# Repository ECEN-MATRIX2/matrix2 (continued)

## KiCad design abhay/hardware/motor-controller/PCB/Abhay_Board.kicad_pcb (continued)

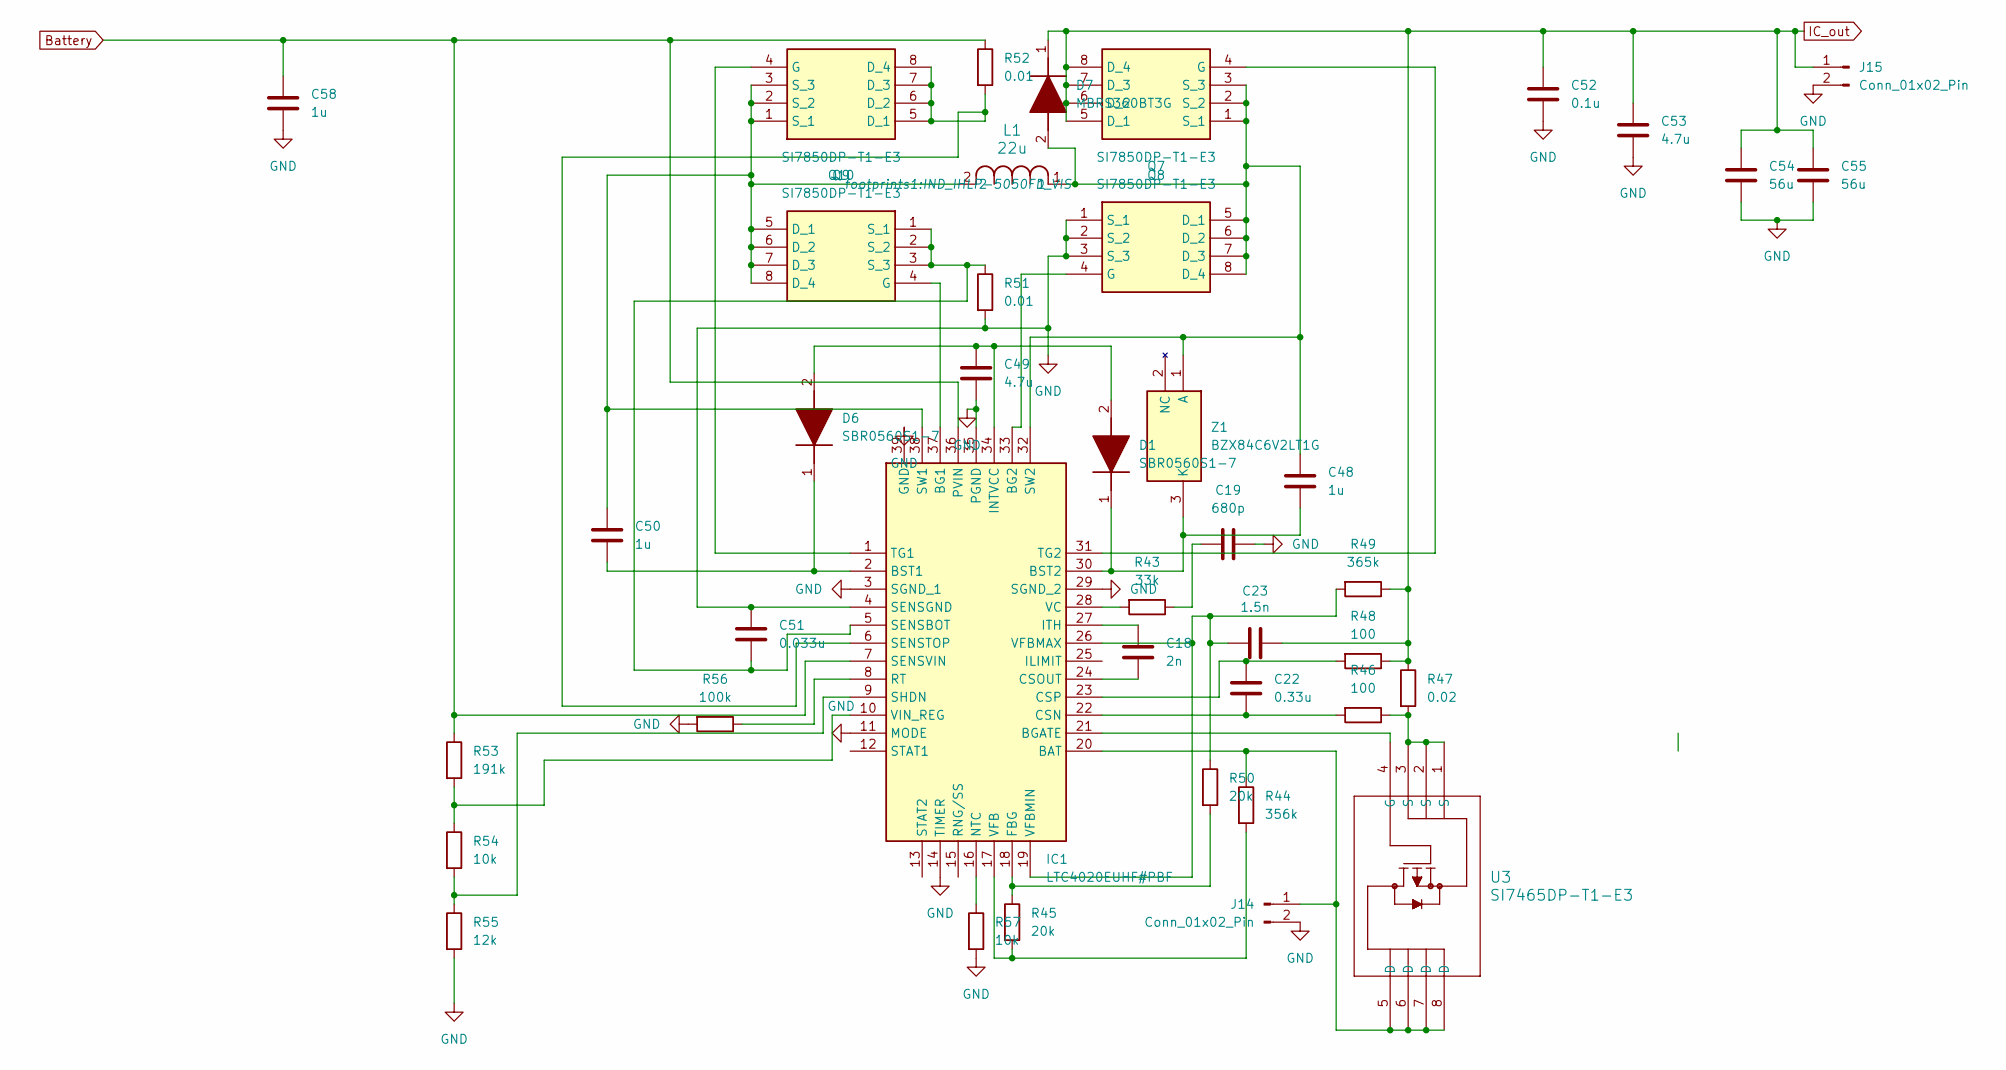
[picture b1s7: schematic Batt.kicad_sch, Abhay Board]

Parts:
C18: 2n; C_1206_3216Metric
C19: 680p; C_0603_1608Metric
C22: 0.33u; C_0603_1608Metric
C23: 1.5n; C_1206_3216Metric
C48, C58: 1u; C_1206_3216Metric
C49, C53: 4.7u; C_1206_3216Metric
C50: 1u; C_0603_1608Metric
C51: 0.033u; C_0603_1608Metric
C52: 0.1u; C_0603_1608Metric
C54, C55: 56u; C_Radial_D10.0mm_H12.5mm_P5.00mm
D1, D6: SBR0560S1-7; SOD3716X135N; Mouser Part Number 621-SBR0560S1-7-F
D7: MBRS360BT3G; DIOM5436X247N; Mouser Part Number 863-MBRS360BT3G
IC1: LTC4020EUHF#PBF; QFN50P500X700X80-39N-D; Mouser Part Number N/A
J14, J15: Conn_01x02_Pin; PinHeader_1x02_P2.54mm_Vertical
L1: 22u; IND_IHLP-5050FD_VIS
Q7, Q8, Q9, Q10: SI7850DP-T1-E3; SI7141DPT1GE3; Mouser Part Number 781-SI7850DP-E3
R43: 33k; R_0603_1608Metric
R44: 356k; R_0603_1608Metric
R45, R50: 20k; R_0603_1608Metric
R46, R48: 100; R_0603_1608Metric
R47: 0.02; R_0603_1608Metric
R49: 365k; R_0603_1608Metric
R51: 0.01; R_0603_1608Metric
R52: 0.01; R_2512_6332Metric
R53: 191k; R_0603_1608Metric
R54, R57: 10k; R_0603_1608Metric
R55: 12k; R_0603_1608Metric
R56: 100k; R_0603_1608Metric
U3: SI7465DP-T1-E3; PowerPAK_SO-8_VIS
Z1: BZX84C6V2LT1G; SOT96P237X111-3N; Mouser Part Number 863-BZX84C6V2LT1G

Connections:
Battery: C58.1, IC1.7 (SENSVIN), IC1.36 (PVIN), R52.1, R53.1; also elsewhere on the board
GND: C19.1, C49.1, C51.1, C52.2, C53.2, C54.2, C55.2, C58.2, IC1.3 (SGND_1), IC1.4 (SENSGND), IC1.11 (MODE), IC1.14 (TIMER), IC1.29 (SGND_2), IC1.35 (PGND), IC1.39 (GND), J14.2, J15.2, Q7.1 (S_1), Q7.2 (S_2), Q7.3 (S_3), R51.2, R55.2, R56.2, R57.2; also elsewhere on the board
IC_out: C23.2, C52.1, C53.1, C54.1, C55.1, D7.1 (K), J15.1, Q8.5 (D_1), Q8.6 (D_2), Q8.7 (D_3), Q8.8 (D_4), R47.1, R48.1, R49.1
unnamed: C19.2, R43.1
unnamed: C49.2, D1.2 (A), D6.2 (A), IC1.34 (INTVCC)
unnamed: C48.2, D1.1 (K), IC1.30 (BST2), Z1.3 (K)
unnamed: C50.2, D6.1 (K), IC1.2 (BST1)
unnamed: C48.1, D7.2 (A), IC1.32 (SW2), L1.1, Q7.5 (D_1), Q7.6 (D_2), Q7.7 (D_3), Q7.8 (D_4), Q8.1 (S_1), Q8.2 (S_2), Q8.3 (S_3), Z1.1 (A)
unnamed: IC1.20 (BAT), J14.1, R44.1, U3.5 (D), U3.6 (D), U3.7 (D), U3.8 (D)
unnamed: IC1.37 (BG1), Q10.4 (G)
unnamed: IC1.33 (BG2), Q7.4 (G)
unnamed: IC1.21 (BGATE), U3.4 (G)
unnamed: C22.2, IC1.22 (CSN), R46.2
unnamed: C18.2, IC1.24 (CSOUT)
unnamed: C22.1, IC1.23 (CSP), R48.2
unnamed: IC1.18 (FBG), R45.1, R50.2
unnamed: C18.1, IC1.27 (ITH)
unnamed: IC1.16 (NTC), R57.1
unnamed: IC1.8 (RT), R56.1
unnamed: C51.2, IC1.5 (SENSBOT), Q10.1 (S_1), Q10.2 (S_2), Q10.3 (S_3), R51.1
unnamed: IC1.6 (SENSTOP), Q9.5 (D_1), Q9.6 (D_2), Q9.7 (D_3), Q9.8 (D_4), R52.2
unnamed: IC1.9 (SHDN), R54.2, R55.1
unnamed: C50.1, IC1.38 (SW1), L1.2, Q9.1 (S_1), Q9.2 (S_2), Q9.3 (S_3), Q10.5 (D_1), Q10.6 (D_2), Q10.7 (D_3), Q10.8 (D_4)
unnamed: IC1.1 (TG1), Q9.4 (G)
unnamed: IC1.31 (TG2), Q8.4 (G)
unnamed: IC1.28 (VC), R43.2
unnamed: IC1.17 (VFB), R44.2, R45.2
unnamed: C23.1, IC1.19 (VFBMIN), IC1.26 (VFBMAX), R49.2, R50.1
unnamed: IC1.10 (VIN_REG), R53.2, R54.1
unnamed: R46.1, R47.2, U3.1 (S), U3.2 (S), U3.3 (S)

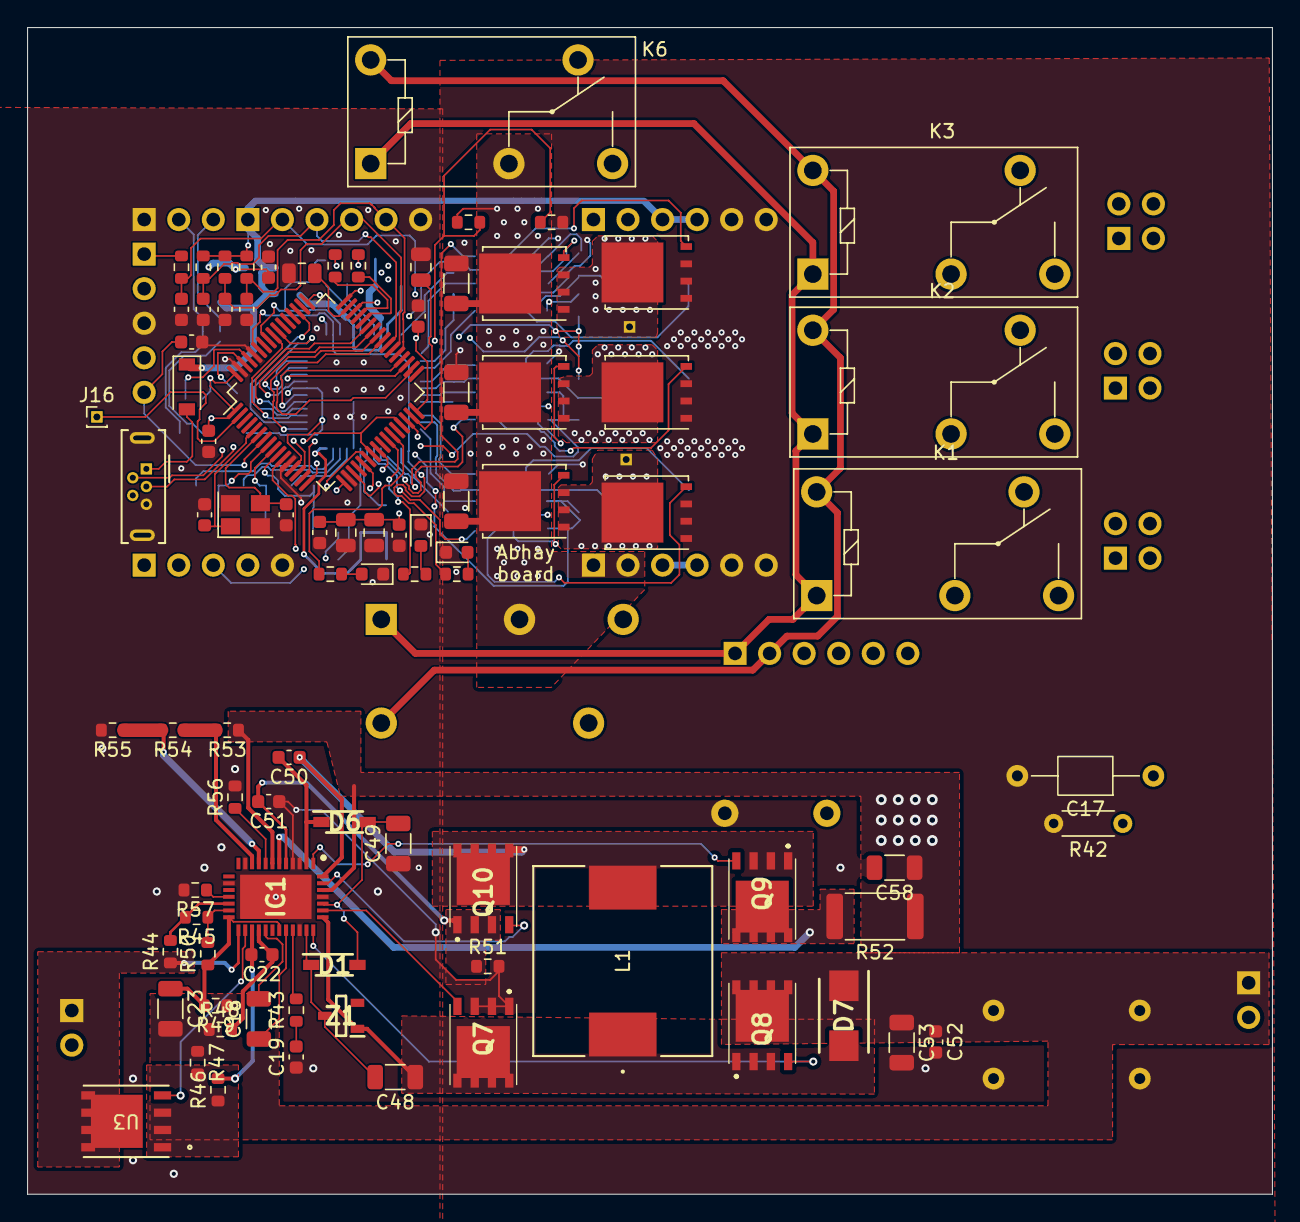
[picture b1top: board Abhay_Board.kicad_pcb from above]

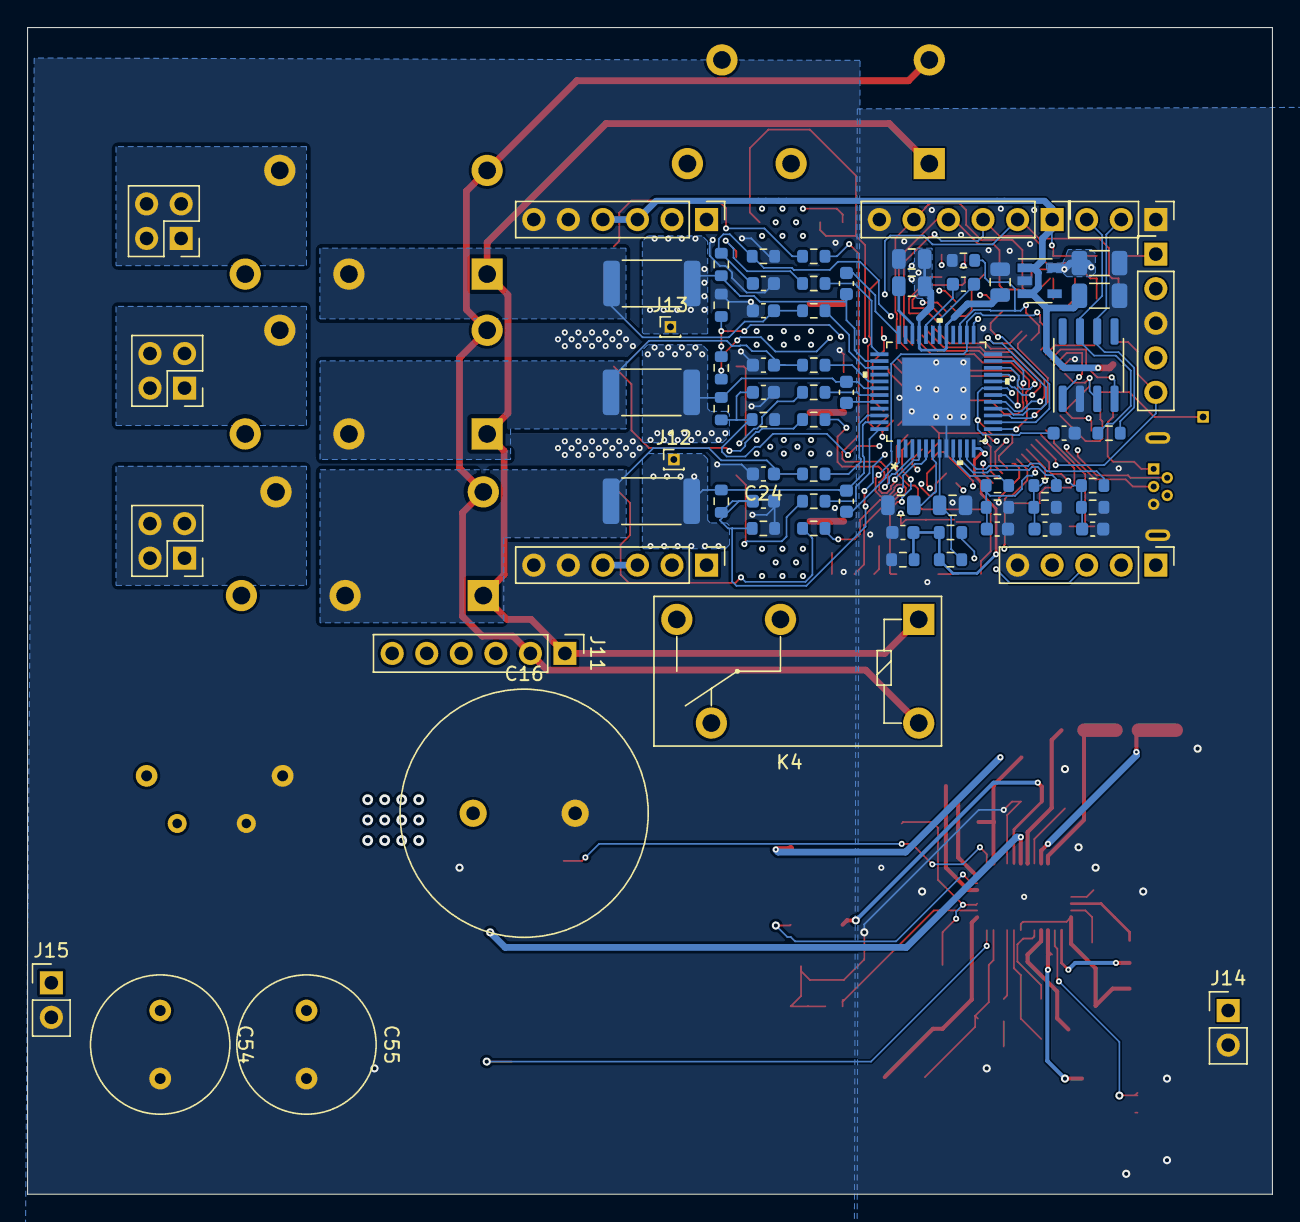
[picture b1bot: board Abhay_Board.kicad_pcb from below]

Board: 4 copper layers, 91.5 x 85.8 mm, 161 parts (74 on the bottom side), 120 nets.

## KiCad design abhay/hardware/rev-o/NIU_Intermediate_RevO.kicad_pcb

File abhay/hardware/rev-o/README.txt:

NIU INTERMEDIATE BOARD - REV O - RELAY 12 V PASS-THROUGH
Prepared 2026-10-08. Extract the complete ZIP, then open NIU_Intermediate_RevO.kicad_pro in KiCad 9.
Local symbol/footprint libraries and all fitted-component 3D models are included.

Rev O adds J14 beside J5. It is a second regular two-pin male header wired
directly in parallel with the external relay-control input, before diode D3.
All Rev N components, their values/MPNs, placements and original traces remain.
The 36 V buck, isolated 5 V, local sensing 3.3 V, SOC circuit and 5 V throttle
are unchanged. J13 remains removed; J14 is NOT a 3.3 V power connector.

  ONE external switched 12 V source -> J5
                                       | parallel, raw +12 V / coil return
                                       +-> J14 -> motor-board J11 pins 1 and 2

Header          Pin 1                    Pin 2
J5 12V IN       external +12 V           external coil return
J14 12V OUT     same external +12 V      same external coil return
Motor J11       Relay+                   Relay-

Connect J14 pin 1 to motor J11 pin 1 and J14 pin 2 to motor J11 pin 2.
Do not add a second power supply to J14, or connect COIL_RET to battery or
SYSTEM_RET. This is a pass-through, not a 12 V regulator. It applies the same
ON/OFF command to both boards and adds no intentional delay.

With five actual 12 V G5Q-1 SPDT motor-board coils, the combined nominal load
is about 0.20 A: 5 x 33.3 mA plus about 37 mA for this board. The motor CAD says
G5Q-1 but does not identify the fitted coil-voltage suffix; verify the parts.
Use a switched 12 V output rated for at least 0.3 A, preferably 0.5 A, and verify
voltage at both boards when all coils are on. This combined load exceeds the
earlier 100 mA preference for the intermediate board alone.
D3 and D4 protect only this board's branch; they do not provide reverse-polarity
or flyback protection for the raw J14 output. Retain/check the motor board and
source driver's appropriate coil suppression. Do not add an unreviewed common
clamp, since suppression can change relay release timing.

U11 generates the sensing interface's 3.3 V locally from the always-on isolated
5 V rail. U11/C36/C37 and the separate battery-domain U10 supply are retained.
No external 3.3 V feed is needed. Mode-switched grounding remains as below.

84 x 128 mm rectangle (3.31 x 5.04 in), four layers, 1 oz copper each layer.
No board growth. 120 fitted components plus four mounting holes: exactly one
extra header versus Rev N. Motor PCB and installed firmware were not modified
or operated while preparing this revision.

Ordering
Purchasing/NIU_RevO_BOM.xlsx: 57 Mouser SKUs, 119 purchased pieces for one board.
User-supplied XT60 makes 120 fitted parts. No spares included.
- New/empty cart: Mouser_RevO_Full_1Board.csv.
- Already bought Rev N: Mouser_RevO_Added_Since_RevN.csv, one extra header.
- Already bought Rev M: Mouser_RevO_Added_Since_RevM.csv, U11/C36/C37 only.
  Reuse the spare two-pin header previously assigned to removed J13 for J14.
- Already bought Rev L: Mouser_RevO_Added_Since_RevL.csv, 34 extra pieces.
Use only the list appropriate to the order already placed.
J14 is Harwin M20-9990245 / Mouser 855-M20-9990245, the existing header SKU.
There are 12 fitted two-pin headers. No new part number is introduced in Rev O.
Prior stock evidence is retained; the increased header quantity was not
rechecked in a live cart. No component or PCB order was placed.

Integration
J12.1 is SDA, J12.2 is SCL. SYSTEM_RET reaches the motor/comm boards through
the existing two-wire 5 V power connections. No connection to motor J3.1
or any other external 3.3 V rail is required. Do not tie 3.3 V regulators together.
SOC requires firmware integration and calibration. FIRMWARE_INTEGRATION.txt
retains the proposed motor-MCU bridge and GNSS-preserving UART arrangement.
That proposal repurposes PA5 from analog speed to software-I2C clock; do not
connect J12 while the old firmware drives PA5 as a DAC.

Power and mode operation
  Battery -> F1 10 A -> R33 sense shunt -> LM70860 synchronous buck -> D7 -> K1 NC -> VM
  Charger output -> R34 sense shunt -> K1 NO -> F3 10 A -> battery charge port
K1 NC 11-12 carries drive positive; NC 21-22 carries drive return.
K1 NO 33-34 carries charge positive; NO 43-44 carries charge return.
Coil 0 is positive; coil 1 is negative. One 12 V / 30 mA nominal coil is powered
only by the external mode source. LED/opto current is additional and the total
is about 37 mA for this board alone. J14 motor-coil current is additional.
12 V absent: NC drive contacts closed, NO charging contacts open.
12 V present: NC drive contacts open, NO charging contacts closed.
The forcibly guided NC/NO mechanism replaces independent relay timing. All four
contacts are used for power paths; there is no feedback contact or welded-contact
diagnostic circuit. This is not a certified complete safety control system.

Keep the external sequence: disable drive before transfer; assert 12 V, wait
one second, then start AC. Stop AC, wait one second, then remove 12 V. No precharge
was added. Near-zero steady load does not eliminate capacitor charging inrush.
The G7SA has a 6 A carry rating, but its full-current resistive DC switching
rating is 6 A at 30 VDC. Its 125 VDC maximum switching voltage is NOT permission
to switch 6 A at 125 V. Loaded 36-54.6 V transfer and capacitive making current
have not been qualified. Measure inrush and obtain an applicable load rating
before using this prototype for repeated high-voltage load transfer.

Isolation meaning
Both conductors of the inactive drive/charge path are disconnected by contacts.
The unchanged motor PCB joins VM, charge-input and MCU returns as SYSTEM_RET.
Battery charge/discharge negatives may also be internally shared. As accepted
by the user, the active mode can connect SYSTEM_RET to that mode's battery return.
U1 provides an isolated conversion barrier, but its output return is SYSTEM_RET;
it does not make MCU/comm/throttle permanently isolated from VM/charging ground.
The external coil circuit remains separate. No mains isolation claim is made.

Voltage and current limits
36 V is the nominal loaded VM target: the buck regulates about 36.48 V before
D7 and the delivered voltage depends on diode drop, load and tolerance. Maximum
battery input is 54.6 V. Nominal enable threshold is about 39.3 V; this buck needs
input headroom and cannot boost a depleted battery.
The converter IC is rated 6 A; this is NOT a 6 A or 10 A complete-board rating.
The two-pin headers are rated 3 A per contact MAXIMUM. The mating jumper contacts
and wire may be rated lower or have no documented current rating. Use an external
current limit chosen for the actual harness. Start bench checks at low current.
The retained 10 A fuses do not protect these jumper wires against overload.
No continuous current or peak-duration qualification has been performed.
The motor PCB's separate phase-contact limits remain unchanged.

D7 still dissipates heat (about 1 W at 2 A, dependent on temperature). Wider
copper does not replace thermal testing. The VM shunt remains limited incidental-
energy protection: about 38.5 V on, 37.5 V off and 0.31 A at threshold. It is not
a regen brake, guaranteed 40 V ceiling, or sustained-backdrive/buck-fault absorber.

Connections: pin 1 / pin 2
J1  XT60 battery positive / battery discharge negative
J2  VM nominal 36 V / SYSTEM_RET
J3  charger-IC output positive / SYSTEM_RET
J4  battery charge-port positive / battery charge-port negative
J5  external charge-mode 12 V INPUT / isolated coil return
J6  MCU 5 V / SYSTEM_RET
J7  communication-board 5 V / SYSTEM_RET
J8  throttle 5 V / SYSTEM_RET
J9  raw throttle signal / SYSTEM_RET
J10 divided throttle ADC signal / SYSTEM_RET
J11 active-low charge command / SYSTEM_RET (MCU 3.3 V pull-up)
J12 SOC SDA / SOC SCL (3.3 V I2C signals, NOT a power connector)
J14 external charge-mode 12 V PASS-THROUGH / isolated coil return
J2-J12 and J14 use regular 2-pin 2.54 mm male headers. They are unkeyed: follow pin numbers
and the +/return markings when mating jumper wires. Auxiliary 5 V stays on in
both modes. J11 is a mode input, not an MCU shutoff or contact-position feedback.
See FIRMWARE_INTEGRATION.txt for the existing motor-board GPIO connection.

Package and CAD checks
Seven schematic sheets, PCB/project, local libraries/models, BOM and ordering
files, schematic PDF, filled-copper/3D previews, Gerbers, PTH/NPTH drills,
assembly positions and verification reports are included.
ERC 0, DRC 0, unconnected 0, parity 0; 334 electrical pads match schematic/model.
45 filled zones, 182 through vias, 237 round holes. Minimum drill 0.30 mm.
No slots, overlapping holes, blind/buried vias or internal cutouts. Projected
3 mm copper spacing checked across all four layers and all isolation domains.
See FABRICATION.txt for the retained AdvancedPCB special process constraints.

Hardware validation
This is a CAD-checked prototype. BENCH_CHECKS.txt retains the existing thermal,
inrush, transient and sensing checks and adds local 3.3 V startup/shutdown tests.
J5/J14 wiring, combined coil load and turn-off transients also require checks.
No assembled Rev O board has been powered or tested.

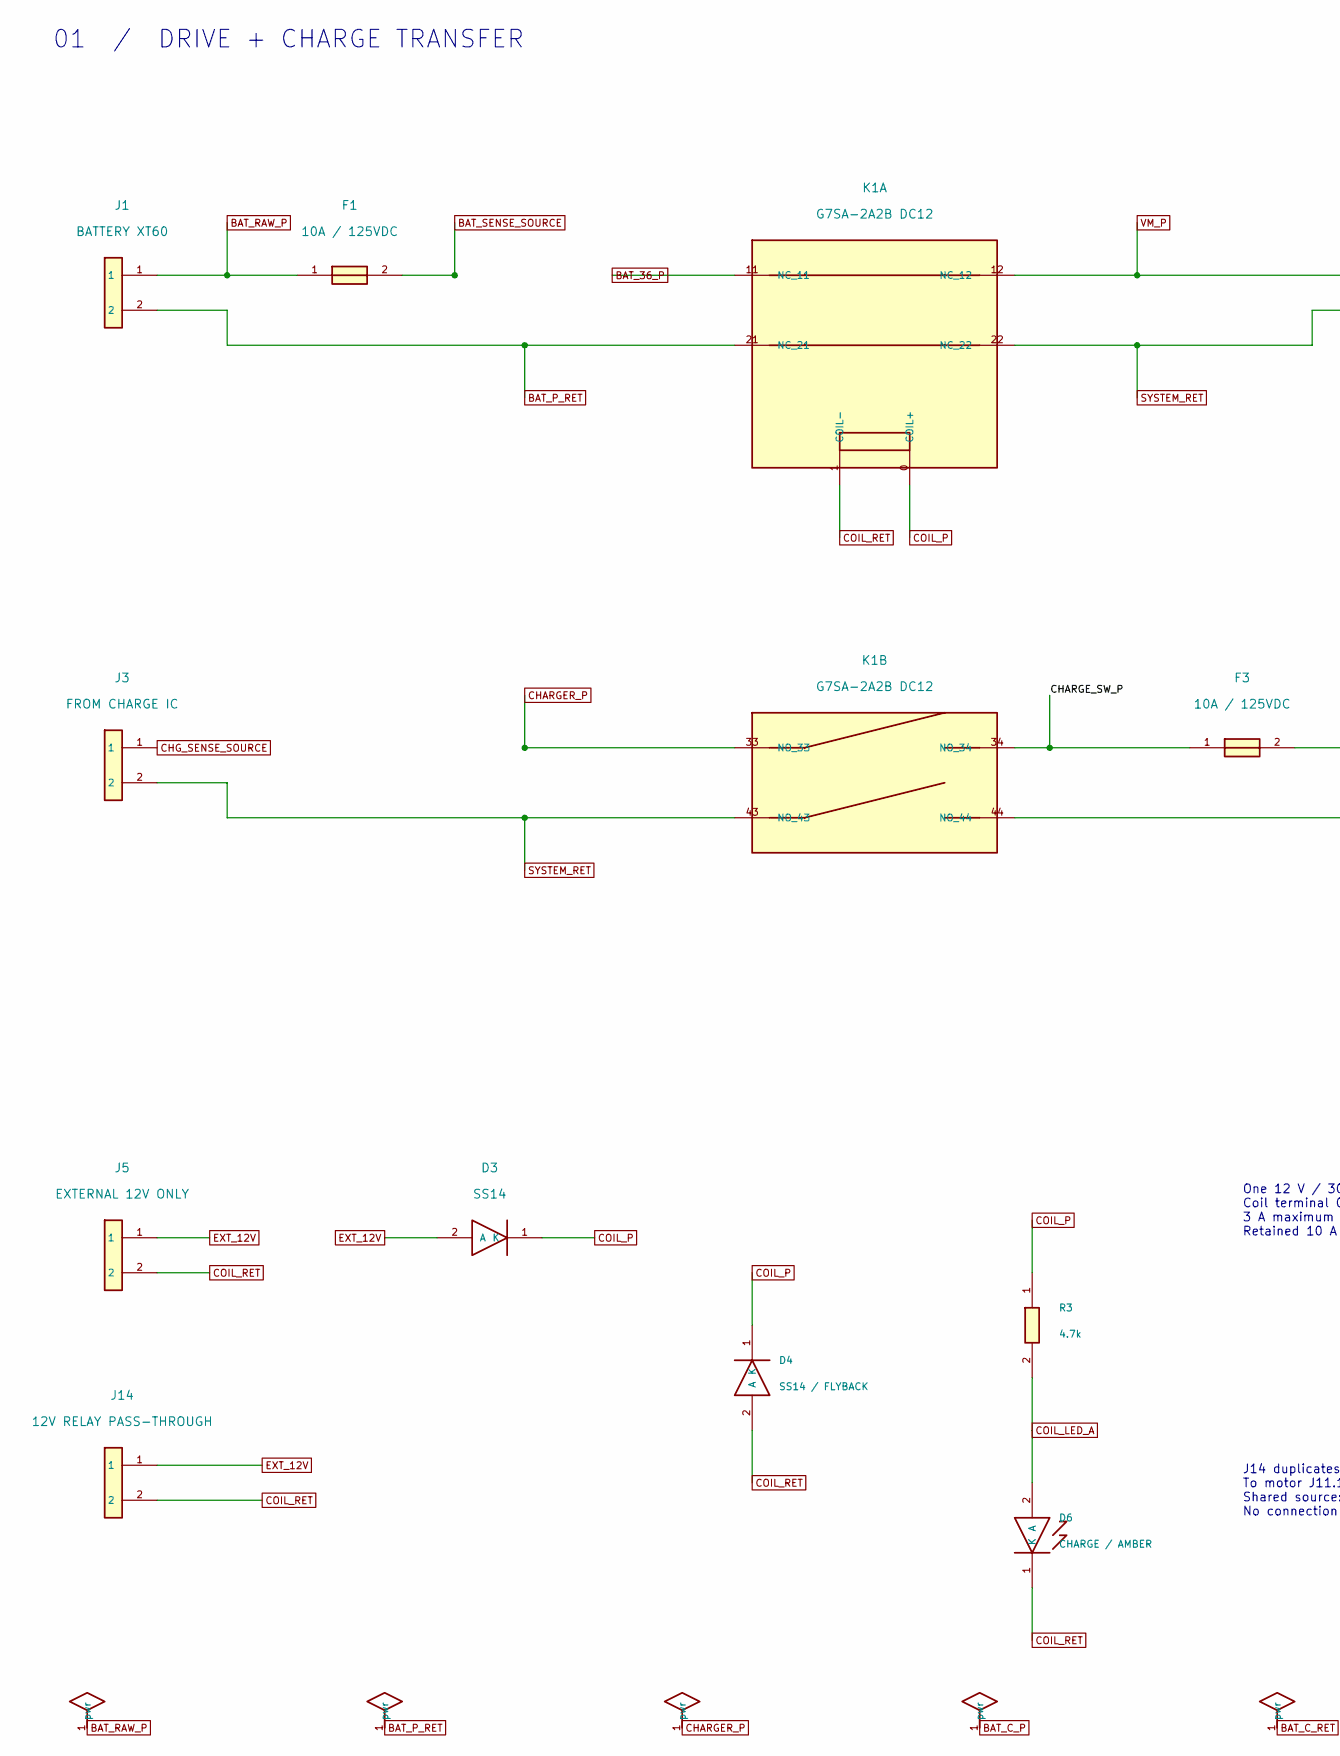
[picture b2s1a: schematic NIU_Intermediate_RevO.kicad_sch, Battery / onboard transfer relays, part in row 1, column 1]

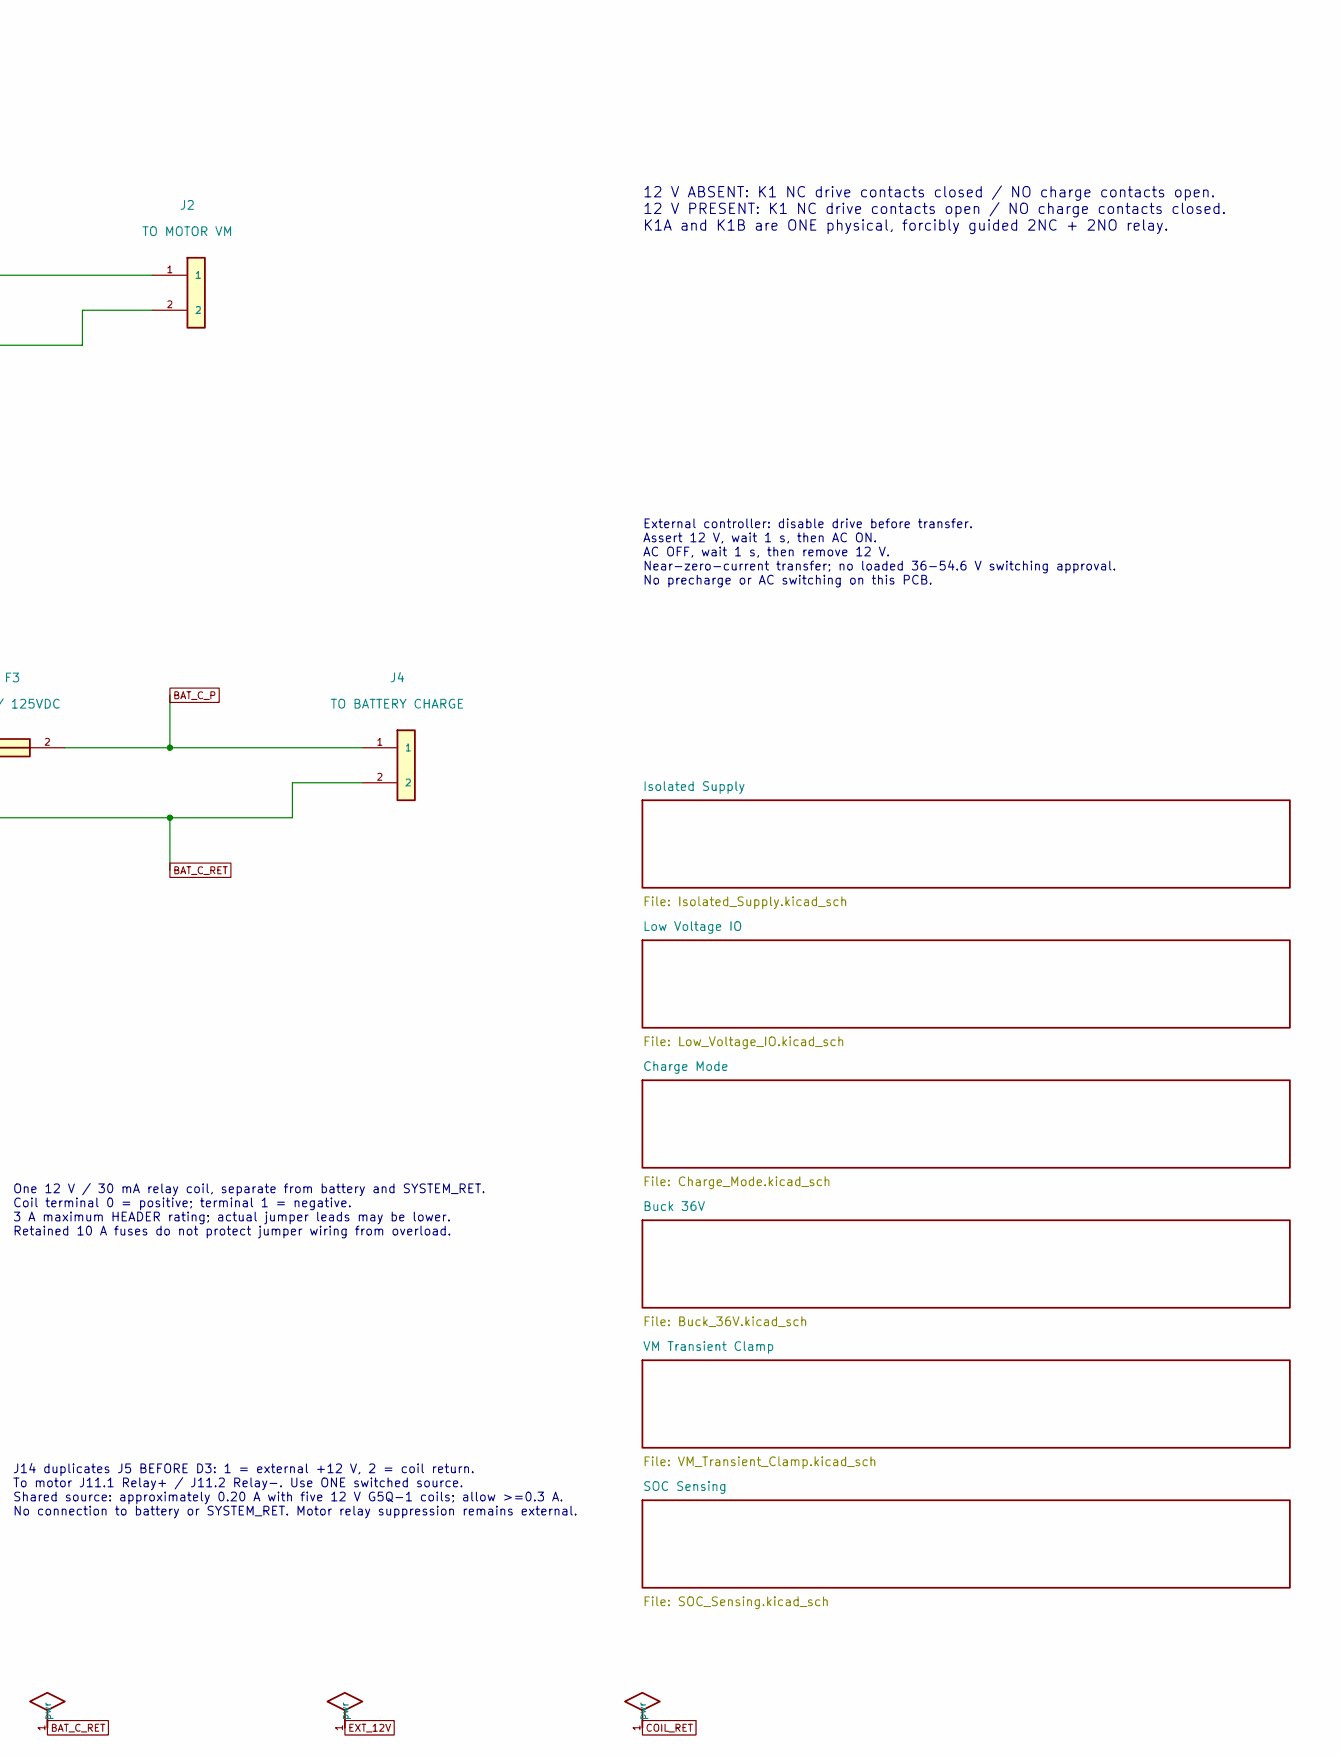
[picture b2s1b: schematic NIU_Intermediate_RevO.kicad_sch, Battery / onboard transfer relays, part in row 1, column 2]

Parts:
D3: SS14; D_SMA; Rating 40V 1A Schottky; MPN SS14-E3/61T; Mouser 625-SS14-E3
D4: SS14 / FLYBACK; D_SMA; Rating 40V 1A Schottky; MPN SS14-E3/61T; Mouser 625-SS14-E3
D6: CHARGE / AMBER; LED_0805_2012Metric; Rating 0805 amber; MPN LTST-C170KSKT; Mouser 859-LTST-C170KSKT
F1, F3: 10A / 125VDC; Fuse_SCHURTER_UMT-H_5.3x16; Rating 10A time lag; Schurter UMT-H; MPN 3403.0284.23; Mouser 693-3403.0284.23
J1: BATTERY XT60; AMASS_XT60-M_Vertical_PositivePin1; Rating 54.6V max intended pack; MPN XT60-M
J2: TO MOTOR VM; PinHeader_1x02_P2.54mm_Vertical; Rating 3A max per header contact; mating lead 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; MPN M20-9990245; Mouser 855-M20-9990245
J3: FROM CHARGE IC; PinHeader_1x02_P2.54mm_Vertical; Rating 3A max per header contact; mating lead 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; MPN M20-9990245; Mouser 855-M20-9990245
J4: TO BATTERY CHARGE; PinHeader_1x02_P2.54mm_Vertical; Rating 3A max per header contact; mating lead 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; MPN M20-9990245; Mouser 855-M20-9990245
J5: EXTERNAL 12V ONLY; PinHeader_1x02_P2.54mm_Vertical; Rating 3A header / LV signals; MPN M20-9990245; Mouser 855-M20-9990245
J14: 12V RELAY PASS-THROUGH; PinHeader_1x02_P2.54mm_Vertical; Rating 3A header / LV signals; MPN M20-9990245; Mouser 855-M20-9990245
K1: G7SA-2A2B DC12; Omron_G7SA_2A2B_TopView; Rating 2NC+2NO forcibly guided; 12V/30mA coil;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; MPN G7SA-2A2B DC12; Mouser 653-G7SA-2A2BDC12
R3: 4.7k; R_0805_2012Metric; Rating 1%, 0.125W; MPN RC0805FR-074K7L; Mouser 603-RC0805FR-074K7L

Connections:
/CHARGE_SW_P: F3.1, K1.34 (NO_34)
BAT_36_P: K1.11 (NC_11); also elsewhere on the board
BAT_C_P: F3.2, J4.1
BAT_C_RET: J4.2, K1.44 (NO_44)
BAT_P_RET: J1.2, K1.21 (NC_21); also elsewhere on the board
BAT_RAW_P: F1.1, J1.1
BAT_SENSE_SOURCE: F1.2; also elsewhere on the board
CHARGER_P: K1.33 (NO_33); also elsewhere on the board
CHG_SENSE_SOURCE: J3.1; also elsewhere on the board
COIL_LED_A: D6.2 (A), R3.2
COIL_P: D3.1 (K), D4.1 (K), K1.0 (COIL+), R3.1; also elsewhere on the board
COIL_RET: D4.2 (A), D6.1 (K), J5.2, J14.2, K1.1 (COIL-); also elsewhere on the board
EXT_12V: D3.2 (A), J5.1, J14.1
SYSTEM_RET: J2.2, J3.2, K1.22 (NC_22), K1.43 (NO_43); also elsewhere on the board
VM_P: J2.1, K1.12 (NC_12); also elsewhere on the board

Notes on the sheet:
01 / DRIVE + CHARGE TRANSFER
12 V ABSENT: K1 NC drive contacts closed / NO charge contacts open. 12 V PRESENT: K1 NC drive contacts open / NO charge contacts closed. K1A and K1B are ONE physical, forcibly guided 2NC + 2NO relay.
External controller: disable drive before transfer. Assert 12 V, wait 1 s, then AC ON. AC OFF, wait 1 s, then remove 12 V. Near-zero-current transfer; no loaded 36-54.6 V switching approval. No precharge or AC switching on this PCB.
One 12 V / 30 mA relay coil, separate from battery and SYSTEM_RET. Coil terminal 0 = positive; terminal 1 = negative. 3 A maximum HEADER rating; actual jumper leads may be lower. Retained 10 A fuses do not protect jumper wiring from overload.
J14 duplicates J5 BEFORE D3: 1 = external +12 V, 2 = coil return. To motor J11.1 Relay+ / J11.2 Relay-. Use ONE switched source. Shared source: approximately 0.20 A with five 12 V G5Q-1 coils; allow >=0.3 A. No connection to battery or SYSTEM_RET. Motor relay suppression remains external.

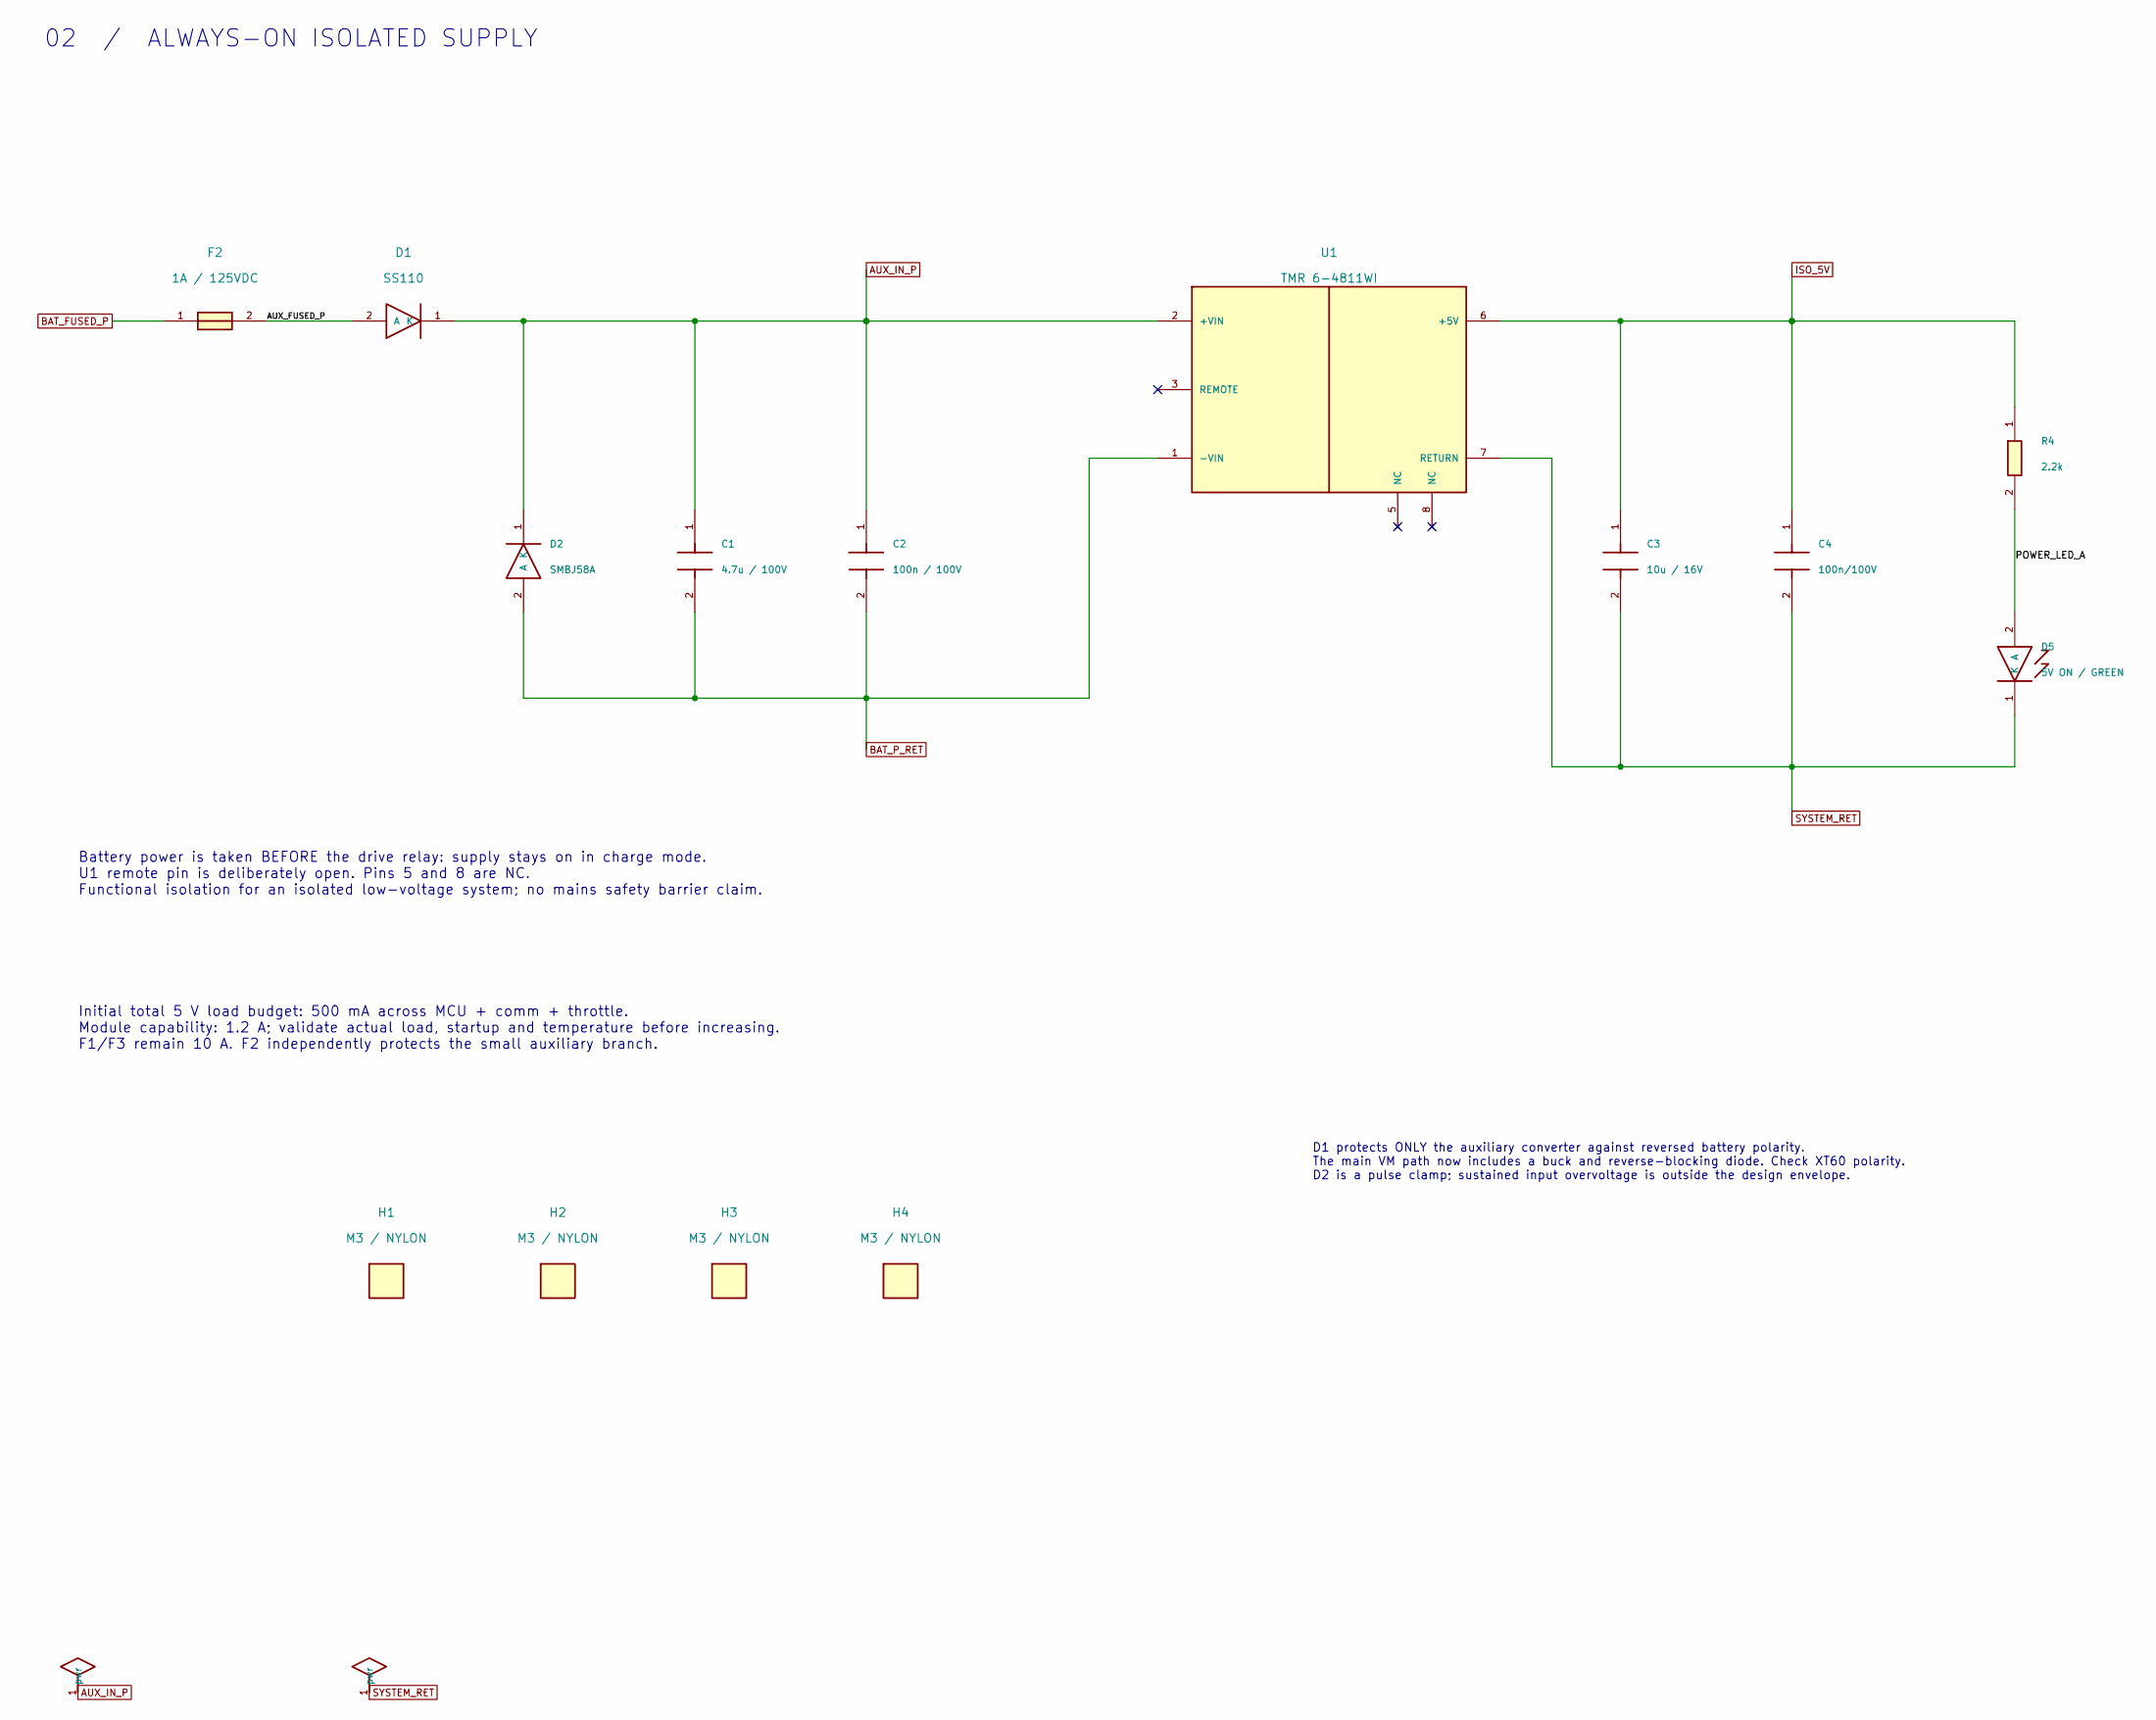
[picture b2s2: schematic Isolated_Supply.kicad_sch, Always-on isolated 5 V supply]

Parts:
C1: 4.7u / 100V; TDK_CNC6_1210_Recommended; Rating X7R, 10%, 1210; 3.2 x 2.5 x 2.5 mm; MPN CNC6P1X7R2A475K250AE; Mouser 810-CNC6P1X7R2A475K2
C2: 100n / 100V; C_0805_2012Metric; Rating X7R, 10%, 0805; MPN C2012X7R2A104K125AA; Mouser 810-C2012X7R2A104K
C3: 10u / 16V; C_0805_2012Metric; Rating X5R, 10%, 0805, 0.85 mm height; MPN C2012X5R1C106K085AC; Mouser 810-C2012X5R1C106K-2
C4: 100n/100V; C_0805_2012Metric; Rating X7R, 10%, 0805; MPN C2012X7R2A104K125AA; Mouser 810-C2012X7R2A104K
D1: SS110; D_SMA; Rating 100V 1A Schottky; MPN SS110-LTP; Mouser 833-SS110-LTP
D2: SMBJ58A; D_SMB; Rating 58V standoff / 93.6V rated pulse clamp; MPN SMBJ58A; Mouser 652-SMBJ58A
D5: 5V ON / GREEN; LED_0805_2012Metric; Rating 0805 green; MPN LTST-C170KGKT; Mouser 859-LTST-C170KGKT
F2: 1A / 125VDC; Fuse_Littelfuse_NANO2_452-454; Rating 1A time lag 125VDC; MPN 0454001.MR; Mouser 576-0454001.MR
H1, H2, H3, H4: M3 / NYLON; MountingHole_3.2mm_M3; Rating 3.2mm NPTH; MPN M3 nylon hardware
R4: 2.2k; R_0805_2012Metric; Rating 1% 0.125W; MPN RC0805FR-072K2L; Mouser 603-RC0805FR-072K2L
U1: TMR 6-4811WI; TRACO_TMR6WI_SIP8_TopView; Rating 18-75Vin; 5V/1.2A; functional isolation; MPN TMR 6-4811WI; Mouser 495-TMR6-4811WI

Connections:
/Isolated Supply/AUX_FUSED_P: D1.2 (A), F2.2
/Isolated Supply/POWER_LED_A: D5.2 (A), R4.2
AUX_IN_P: C1.1, C2.1, D1.1 (K), D2.1 (K), U1.2 (+VIN); also elsewhere on the board
BAT_FUSED_P: F2.1; also elsewhere on the board
BAT_P_RET: C1.2, C2.2, D2.2 (A), U1.1 (-VIN); also elsewhere on the board
ISO_5V: C3.1, C4.1, R4.1, U1.6 (+5V); also elsewhere on the board
SYSTEM_RET: C3.2, C4.2, D5.1 (K), U1.7 (RETURN); also elsewhere on the board

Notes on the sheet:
02 / ALWAYS-ON ISOLATED SUPPLY
Battery power is taken BEFORE the drive relay: supply stays on in charge mode. U1 remote pin is deliberately open. Pins 5 and 8 are NC. Functional isolation for an isolated low-voltage system; no mains safety barrier claim.
Initial total 5 V load budget: 500 mA across MCU + comm + throttle. Module capability: 1.2 A; validate actual load, startup and temperature before increasing. F1/F3 remain 10 A. F2 independently protects the small auxiliary branch.
D1 protects ONLY the auxiliary converter against reversed battery polarity. The main VM path now includes a buck and reverse-blocking diode. Check XT60 polarity. D2 is a pulse clamp; sustained input overvoltage is outside the design envelope.
